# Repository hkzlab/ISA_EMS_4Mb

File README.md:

# ISA 4Mb EMS / ROM Adapter

## Introduction

This is a reimplementation of the **lo-tech.co.uk** [2Mb ISA EMS board](https://www.lo-tech.co.uk/wiki/Lo-tech_2MB_EMS_Board) with small changes:

- All components are thru-hole instead of SMD
- Maximum installable memory expanded to 4Mb
- Activity led to indicate when the memory is accessed
- Optional ROM expansion (had some free space on the PCB...)

### Disclaimer

I take NO responsibility for what happens if you decide to build and use this card. Your computer might crash, catch fire or be destroyed in other nasty ways.
Also, as this card is mostly based on the work of others, You're encourauged to take what you deem fit from this, and use it in your projects!

Additionally, do **NOT CONTACT lo-tech.co.uk FOR SUPPORT**, while this board is derived from their work, it is not their product, please do not waste their time.

## Configuration

### EMS

To configure the EMS, jumpers on J2 header are used.

Pins 1 and 2 configure the Page Frame base address, while 3 and 4 configure the IO Port base address.

```text

EMS Page Frame Base
 1 | 2 | Base  |
---+---+-------+
 X | X | C000h |
---+---+-------+
   | X | D000h |
---+---+-------+
 X |   | E000h |
---+---+-------+
   |   | Inval |
---+---+-------+

EMS IO Port Base
 3 | 4 |   Base     |
---+---+------------+
 X | X |  260-263h  |
---+---+------------+
   | X |  264-267h  |
---+---+------------+
 X |   |  268-26Bh  |
---+---+------------+
   |   |  26C-26Fh  |
---+---+------------+

```

### ROM

To configure the expansion ROM, jumpers on J3 header are used.

The `ENA` pin will enable the ROM when jumpered.

When `32K` pin is jumpered, only 32Kb of the ROM will be used. The ROM can be made to appear at the following addresses:

```text
       | A18 | A17 | A16 | A15 |
-------+-----+-----+-----+-----+
 A000h |  X  |     |  X  |  X  |
-------+-----+-----+-----+-----+
 A800h |  X  |     |  X  |     | (32K only)
-------+-----+-----+-----+-----+
 B000h |  X  |     |     |  X  |
-------+-----+-----+-----+-----+
 B800h |  X  |     |     |     | (32K only)
-------+-----+-----+-----+-----+
 C000h |     |  X  |  X  |  X  |
-------+-----+-----+-----+-----+
 C800h |     |  X  |  X  |     | (32K only)
-------+-----+-----+-----+-----+
 D000h |     |  X  |     |  X  |
-------+-----+-----+-----+-----+
 D800h |     |  X  |     |     | (32K only)
-------+-----+-----+-----+-----+
 E000h |     |     |  X  |  X  |
-------+-----+-----+-----+-----+
 E800h |     |     |  X  |     | (32K only)
-------+-----+-----+-----+-----+
 F000h |     |     |     |  X  |
-------+-----+-----+-----+-----+
 F800h |     |     |     |     | (32K only)
-------+-----+-----+-----+-----+
```

## Usage

You need a **memory manager** to use this board. The original `LTEMM` driver provided by lo-tech only supports up to 2Mb. You can find a modified version under the `software` directory of this repository that supports up to 4Mb (actually 4080Kb or 255 pages, to support all 256 pages I need to rework the detection logic a bit... will get around to it in the future).

## Bill of Materials

All ICs are in DIP package.

If you don't need the expansion ROM feature, you can omit C19, C20, U1, U2, RN1, R1, R2 and J3.

- U1, U7, U8: 74HCT688
- U2: SST39SF010
- U3, U4, U5, U6, U13, U14. U15, U16: AS6C4008 (You don't need to fill all sockets: fit as much memory as you need starting from socket 1!)
- U11: 74HC04 (HCT is fine too)
- U9: 74HCT139
- U10: 74HCT32
- U12: 74ACT245
- U17: 74HCT138
- U18, U19, U20, U21: 74HCT573
- RN1: res. network, 10k, bussed, 6 pins
- RN2: res. network, 10k, bussed, 5 pins
- RN3: res. network, 10k, bussed, 9 pins.
- R1, R2: 10k resistor
- R3: ~470-1k resistor (depends on the type of LED mounted on D1 and desired brightness)
- D1: 3.0mm or 5.0mm LED
- J2 2x4 2.5mm breakable header
- J3 2x7 2.5mm breakable header
- C5, C6: 10uF / 50v electrolytic caps
- Remaining caps: 22x 100nF, ceramic
- ISA bracket: Keystone 9202, plus screws

## Known Issues

I have received reports of this board being unstable when used with some homebrew PC clones, reports included the Xi8088 and NuXT. I have noted similar issues on a Micro8088. On the other hand, an all-CMOS board was tested fine on multiple AT clones I have.
Replacing the following ICs with ones from the TTL family solved the issue for me and for others: U7, U8, U9, U10, U11, U12.

Note that, for increased stability, I use an ISA terminator with these homebrew computers.

Note that the EEPROM U2 has no buffers on the data output. This can cause instability on loaded/noisy buses. Support for the EEPROM will be removed in newer iterations of this board to produce a smaller variant.

## Credits

- Thanks to [lo-tech.co.uk](https://www.lo-tech.co.uk/) for having published their schematics
- Thanks to [Sergey](http://www.malinov.com/Home/sergeys-projects) for all his projects!

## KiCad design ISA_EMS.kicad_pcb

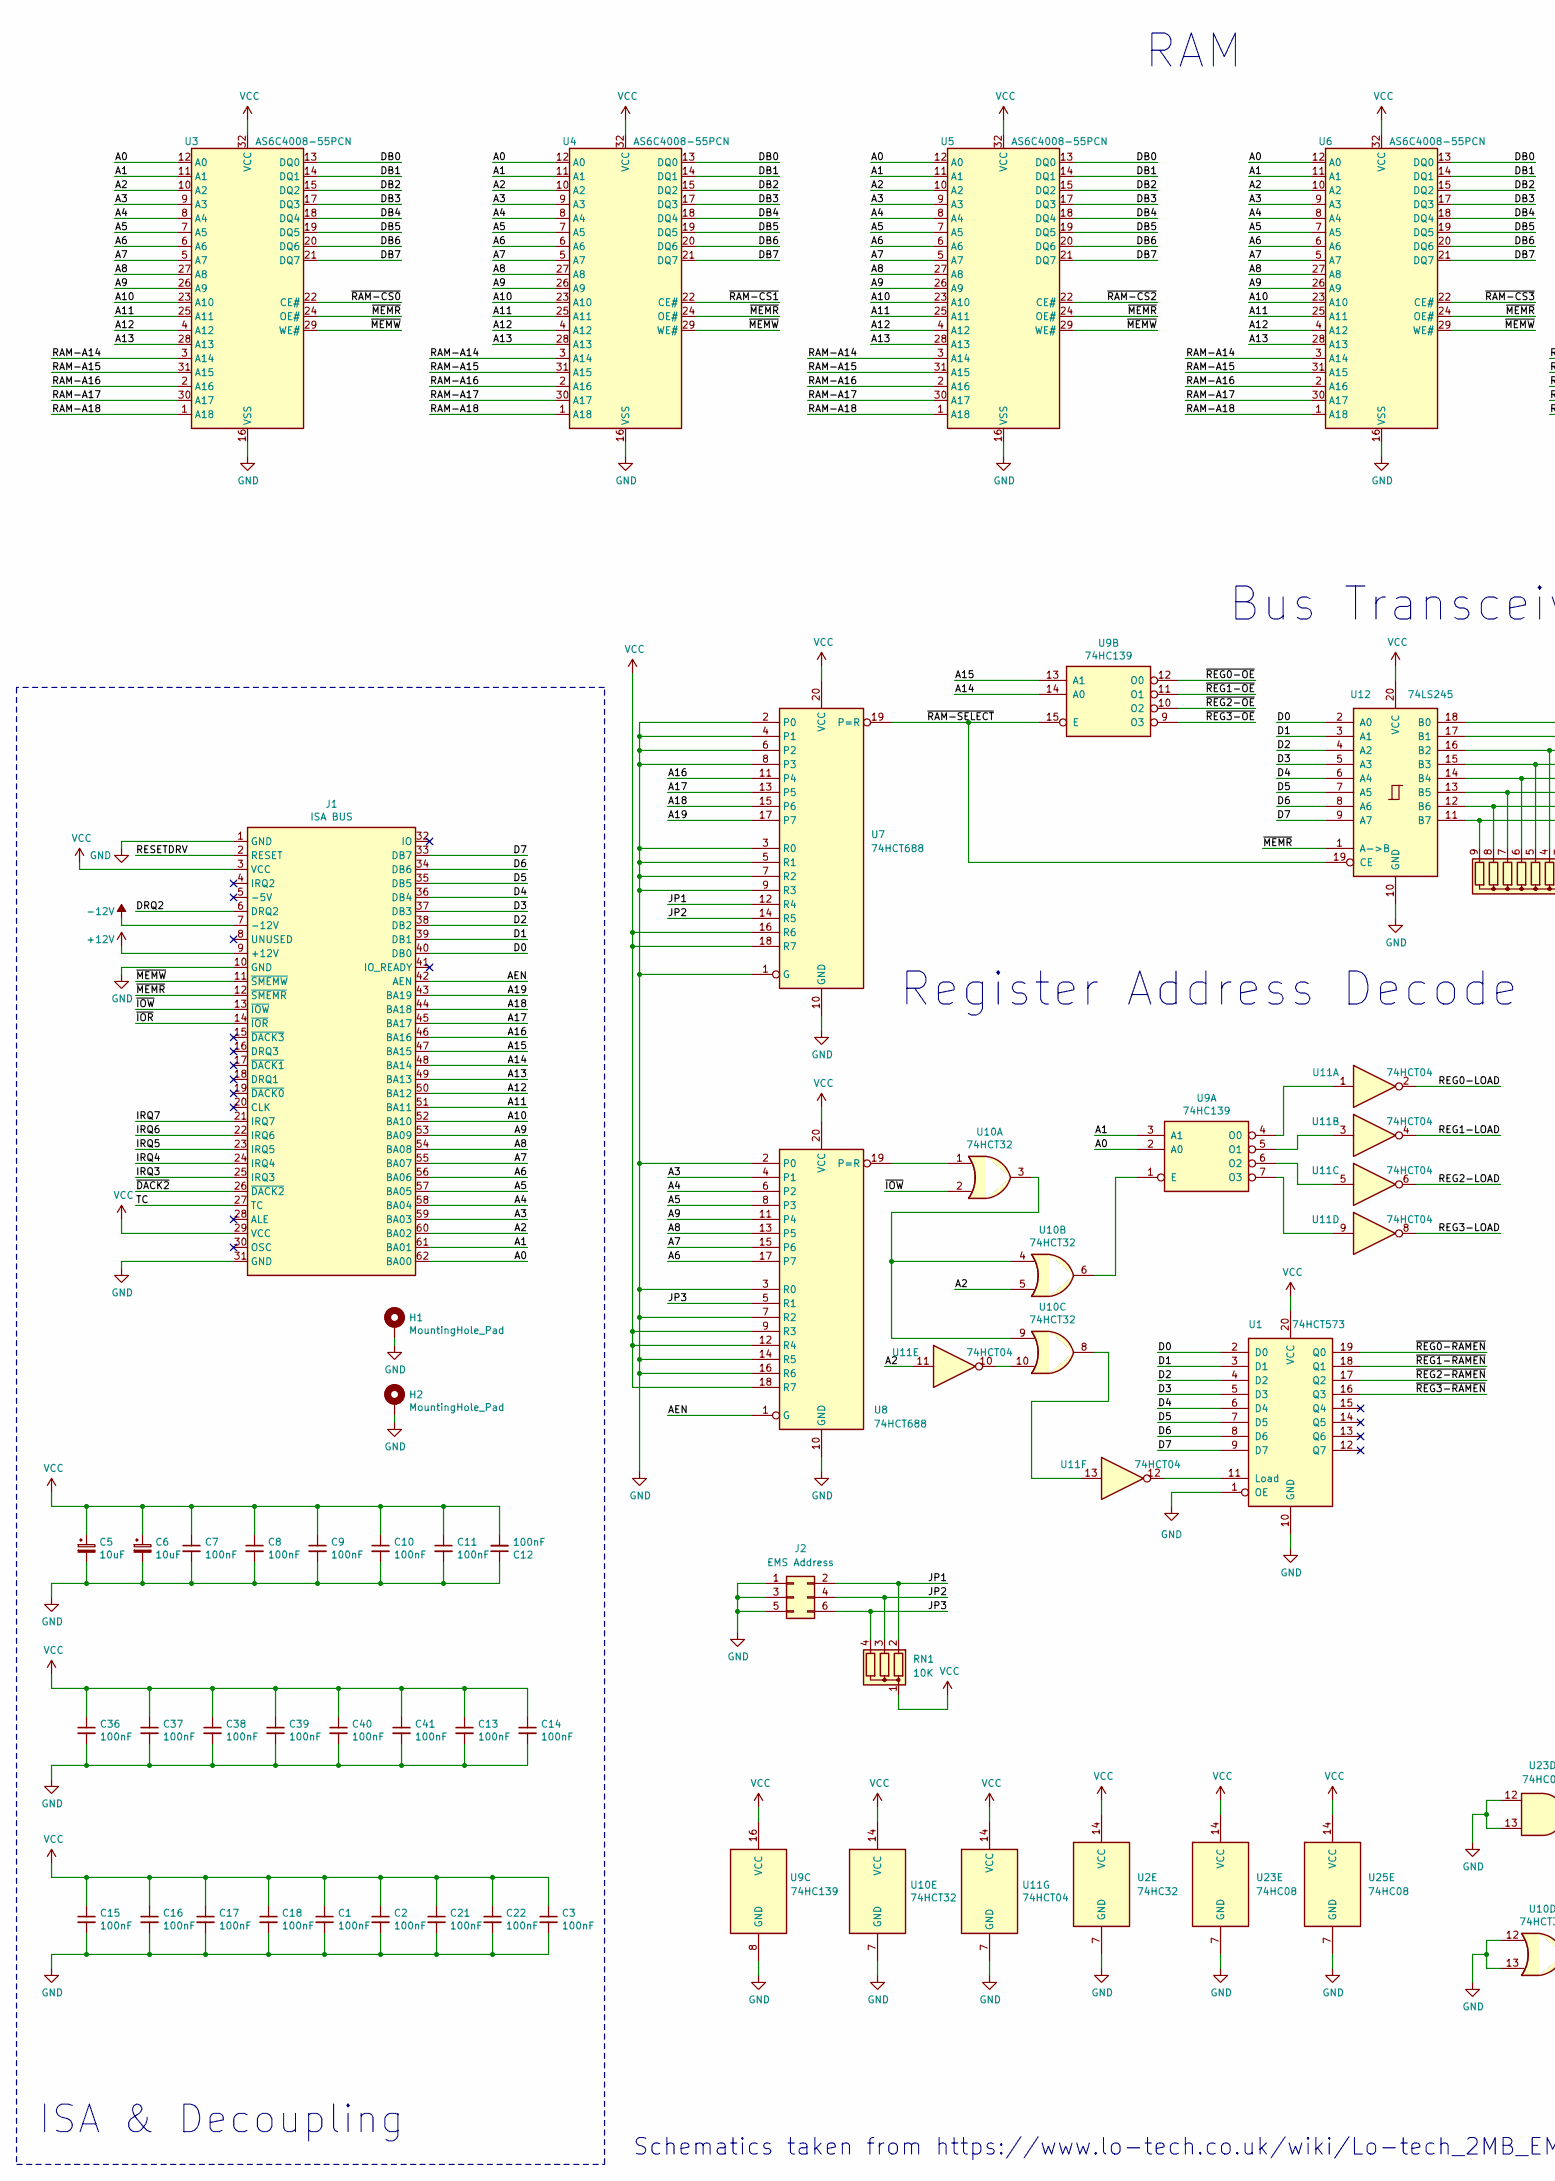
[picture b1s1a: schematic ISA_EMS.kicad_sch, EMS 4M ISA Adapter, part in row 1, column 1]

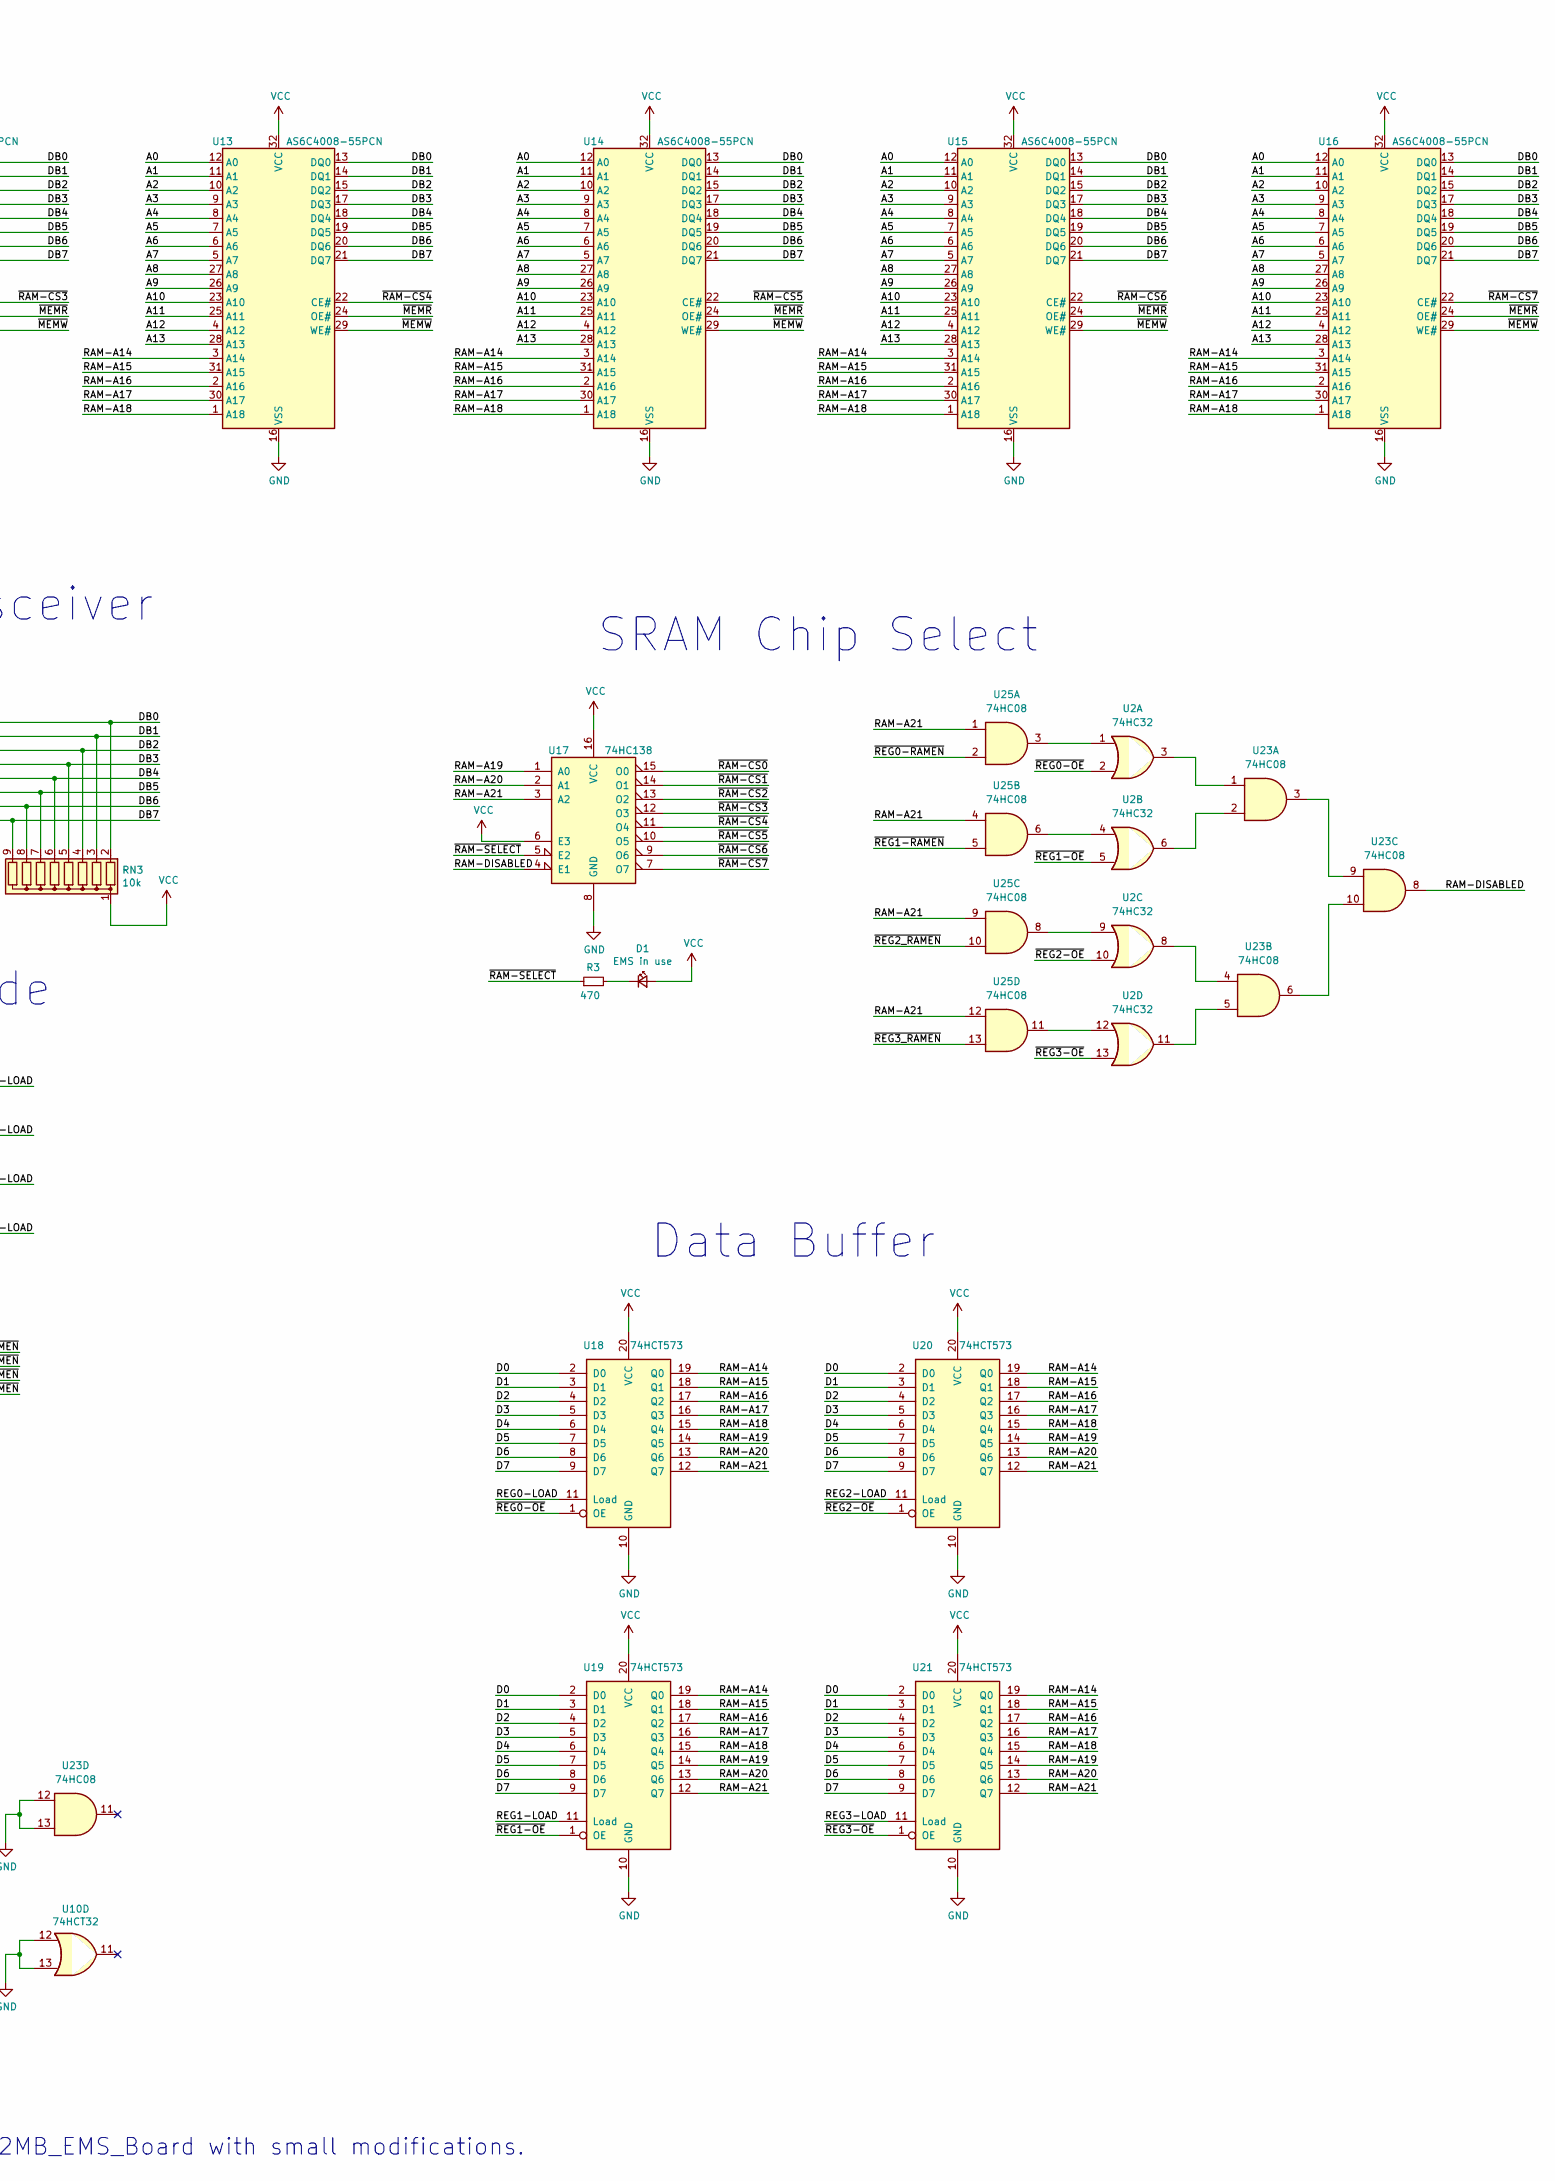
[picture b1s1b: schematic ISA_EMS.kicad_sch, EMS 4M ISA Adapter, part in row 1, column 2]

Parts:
C1, C2, C3, C7, C8, C9, C10, C11, C12, C13, C14, C15, C16, C17, C18, C21, C22, C36, C37, C38, C39, C40, C41: 100nF; C_1206_3216Metric_Pad1.33x1.80mm_HandSolder
C5, C6: 10uF; CP_Radial_D5.0mm_P2.50mm
D1: EMS in use; LED_D3.0mm_Clear
H1, H2: MountingHole_Pad; Hole_3mm
J1: ISA BUS; Conn_Edge_PCB_ISA8
J2: EMS Address; PinHeader_2x03_P2.54mm_Vertical
R3: 470; R_Axial_DIN0207_L6.3mm_D2.5mm_P10.16mm_Horizontal
RN1: 10K; R_Array_SIP4
RN3: 10k; R_Array_SIP9
U1, U18, U19, U20, U21: 74HCT573; DIP-20_W7.62mm
U2: 74HC32; DIP-14_W7.62mm
U3, U4, U5, U6, U13, U14, U15, U16: AS6C4008-55PCN; DIP-32_W15.24mm
U7, U8: 74HCT688; DIP-20_W7.62mm
U9: 74HC139; DIP-16_W7.62mm
U10: 74HCT32; DIP-14_W7.62mm
U11: 74HCT04; DIP-14_W7.62mm
U12: 74LS245; DIP-20_W7.62mm
U17: 74HC138; DIP-16_W7.62mm
U23, U25: 74HC08; DIP-14_W7.62mm

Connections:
+12V: J1.9 (+12V)
-12V: J1.7 (-12V)
/A0: J1.62 (BA00), U3.12 (A0), U4.12 (A0), U5.12 (A0), U6.12 (A0), U9.2 (A0), U13.12 (A0), U14.12 (A0), U15.12 (A0), U16.12 (A0)
/A1: J1.61 (BA01), U3.11 (A1), U4.11 (A1), U5.11 (A1), U6.11 (A1), U9.3 (A1), U13.11 (A1), U14.11 (A1), U15.11 (A1), U16.11 (A1)
/A2: J1.60 (BA02), U3.10 (A2), U4.10 (A2), U5.10 (A2), U6.10 (A2), U10.5, U11.11, U13.10 (A2), U14.10 (A2), U15.10 (A2), U16.10 (A2)
/A3: J1.59 (BA03), U3.9 (A3), U4.9 (A3), U5.9 (A3), U6.9 (A3), U8.4 (P1), U13.9 (A3), U14.9 (A3), U15.9 (A3), U16.9 (A3)
/A4: J1.58 (BA04), U3.8 (A4), U4.8 (A4), U5.8 (A4), U6.8 (A4), U8.6 (P2), U13.8 (A4), U14.8 (A4), U15.8 (A4), U16.8 (A4)
/A5: J1.57 (BA05), U3.7 (A5), U4.7 (A5), U5.7 (A5), U6.7 (A5), U8.8 (P3), U13.7 (A5), U14.7 (A5), U15.7 (A5), U16.7 (A5)
/A6: J1.56 (BA06), U3.6 (A6), U4.6 (A6), U5.6 (A6), U6.6 (A6), U8.17 (P7), U13.6 (A6), U14.6 (A6), U15.6 (A6), U16.6 (A6)
/A7: J1.55 (BA07), U3.5 (A7), U4.5 (A7), U5.5 (A7), U6.5 (A7), U8.15 (P6), U13.5 (A7), U14.5 (A7), U15.5 (A7), U16.5 (A7)
/A8: J1.54 (BA08), U3.27 (A8), U4.27 (A8), U5.27 (A8), U6.27 (A8), U8.13 (P5), U13.27 (A8), U14.27 (A8), U15.27 (A8), U16.27 (A8)
/A9: J1.53 (BA09), U3.26 (A9), U4.26 (A9), U5.26 (A9), U6.26 (A9), U8.11 (P4), U13.26 (A9), U14.26 (A9), U15.26 (A9), U16.26 (A9)
/A10: J1.52 (BA10), U3.23 (A10), U4.23 (A10), U5.23 (A10), U6.23 (A10), U13.23 (A10), U14.23 (A10), U15.23 (A10), U16.23 (A10)
/A11: J1.51 (BA11), U3.25 (A11), U4.25 (A11), U5.25 (A11), U6.25 (A11), U13.25 (A11), U14.25 (A11), U15.25 (A11), U16.25 (A11)
/A12: J1.50 (BA12), U3.4 (A12), U4.4 (A12), U5.4 (A12), U6.4 (A12), U13.4 (A12), U14.4 (A12), U15.4 (A12), U16.4 (A12)
/A13: J1.49 (BA13), U3.28 (A13), U4.28 (A13), U5.28 (A13), U6.28 (A13), U13.28 (A13), U14.28 (A13), U15.28 (A13), U16.28 (A13)
/A14: J1.48 (BA14), U9.14 (A0)
/A15: J1.47 (BA15), U9.13 (A1)
/A16: J1.46 (BA16), U7.11 (P4)
/A17: J1.45 (BA17), U7.13 (P5)
/A18: J1.44 (BA18), U7.15 (P6)
/A19: J1.43 (BA19), U7.17 (P7)
/AEN: J1.42 (AEN), U8.1 (G)
/D0: J1.40 (DB0), U1.2 (D0), U12.2 (A0), U18.2 (D0), U19.2 (D0), U20.2 (D0), U21.2 (D0)
/D1: J1.39 (DB1), U1.3 (D1), U12.3 (A1), U18.3 (D1), U19.3 (D1), U20.3 (D1), U21.3 (D1)
/D2: J1.38 (DB2), U1.4 (D2), U12.4 (A2), U18.4 (D2), U19.4 (D2), U20.4 (D2), U21.4 (D2)
/D3: J1.37 (DB3), U1.5 (D3), U12.5 (A3), U18.5 (D3), U19.5 (D3), U20.5 (D3), U21.5 (D3)
/D4: J1.36 (DB4), U1.6 (D4), U12.6 (A4), U18.6 (D4), U19.6 (D4), U20.6 (D4), U21.6 (D4)
/D5: J1.35 (DB5), U1.7 (D5), U12.7 (A5), U18.7 (D5), U19.7 (D5), U20.7 (D5), U21.7 (D5)
/D6: J1.34 (DB6), U1.8 (D6), U12.8 (A6), U18.8 (D6), U19.8 (D6), U20.8 (D6), U21.8 (D6)
/D7: J1.33 (DB7), U1.9 (D7), U12.9 (A7), U18.9 (D7), U19.9 (D7), U20.9 (D7), U21.9 (D7)
/DB0: RN3.2 (R1), U3.13 (DQ0), U4.13 (DQ0), U5.13 (DQ0), U6.13 (DQ0), U12.18 (B0), U13.13 (DQ0), U14.13 (DQ0), U15.13 (DQ0), U16.13 (DQ0)
/DB1: RN3.3 (R2), U3.14 (DQ1), U4.14 (DQ1), U5.14 (DQ1), U6.14 (DQ1), U12.17 (B1), U13.14 (DQ1), U14.14 (DQ1), U15.14 (DQ1), U16.14 (DQ1)
/DB2: RN3.4 (R3), U3.15 (DQ2), U4.15 (DQ2), U5.15 (DQ2), U6.15 (DQ2), U12.16 (B2), U13.15 (DQ2), U14.15 (DQ2), U15.15 (DQ2), U16.15 (DQ2)
/DB3: RN3.5 (R4), U3.17 (DQ3), U4.17 (DQ3), U5.17 (DQ3), U6.17 (DQ3), U12.15 (B3), U13.17 (DQ3), U14.17 (DQ3), U15.17 (DQ3), U16.17 (DQ3)
/DB4: RN3.6 (R5), U3.18 (DQ4), U4.18 (DQ4), U5.18 (DQ4), U6.18 (DQ4), U12.14 (B4), U13.18 (DQ4), U14.18 (DQ4), U15.18 (DQ4), U16.18 (DQ4)
/DB5: RN3.7 (R6), U3.19 (DQ5), U4.19 (DQ5), U5.19 (DQ5), U6.19 (DQ5), U12.13 (B5), U13.19 (DQ5), U14.19 (DQ5), U15.19 (DQ5), U16.19 (DQ5)
/DB6: RN3.8 (R7), U3.20 (DQ6), U4.20 (DQ6), U5.20 (DQ6), U6.20 (DQ6), U12.12 (B6), U13.20 (DQ6), U14.20 (DQ6), U15.20 (DQ6), U16.20 (DQ6)
/DB7: RN3.9 (R8), U3.21 (DQ7), U4.21 (DQ7), U5.21 (DQ7), U6.21 (DQ7), U12.11 (B7), U13.21 (DQ7), U14.21 (DQ7), U15.21 (DQ7), U16.21 (DQ7)
/DRQ2: J1.6 (DRQ2)
/IRQ3: J1.25 (IRQ3)
/IRQ4: J1.24 (IRQ4)
/IRQ5: J1.23 (IRQ5)
/IRQ6: J1.22 (IRQ6)
/IRQ7: J1.21 (IRQ7)
/JP1: J2.2, RN1.2 (R1), U7.12 (R4)
/JP2: J2.4, RN1.3 (R2), U7.14 (R5)
/JP3: J2.6, RN1.4 (R3), U8.5 (R1)
/RAM-A14: U3.3 (A14), U4.3 (A14), U5.3 (A14), U6.3 (A14), U13.3 (A14), U14.3 (A14), U15.3 (A14), U16.3 (A14), U18.19 (Q0), U19.19 (Q0), U20.19 (Q0), U21.19 (Q0)
/RAM-A15: U3.31 (A15), U4.31 (A15), U5.31 (A15), U6.31 (A15), U13.31 (A15), U14.31 (A15), U15.31 (A15), U16.31 (A15), U18.18 (Q1), U19.18 (Q1), U20.18 (Q1), U21.18 (Q1)
/RAM-A16: U3.2 (A16), U4.2 (A16), U5.2 (A16), U6.2 (A16), U13.2 (A16), U14.2 (A16), U15.2 (A16), U16.2 (A16), U18.17 (Q2), U19.17 (Q2), U20.17 (Q2), U21.17 (Q2)
/RAM-A17: U3.30 (A17), U4.30 (A17), U5.30 (A17), U6.30 (A17), U13.30 (A17), U14.30 (A17), U15.30 (A17), U16.30 (A17), U18.16 (Q3), U19.16 (Q3), U20.16 (Q3), U21.16 (Q3)
/RAM-A18: U3.1 (A18), U4.1 (A18), U5.1 (A18), U6.1 (A18), U13.1 (A18), U14.1 (A18), U15.1 (A18), U16.1 (A18), U18.15 (Q4), U19.15 (Q4), U20.15 (Q4), U21.15 (Q4)
/RAM-A19: U17.1 (A0), U18.14 (Q5), U19.14 (Q5), U20.14 (Q5), U21.14 (Q5)
/RAM-A20: U17.2 (A1), U18.13 (Q6), U19.13 (Q6), U20.13 (Q6), U21.13 (Q6)
/RAM-A21: U17.3 (A2), U18.12 (Q7), U19.12 (Q7), U20.12 (Q7), U21.12 (Q7), U25.1, U25.4, U25.9, U25.12
/RAM-DISABLED: U17.4 (E1), U23.8
/REG0-LOAD: U11.2, U18.11 (Load)
/REG1-LOAD: U11.4, U19.11 (Load)
/REG2-LOAD: U11.6, U20.11 (Load)
/REG3-LOAD: U11.8, U21.11 (Load)
/RESETDRV: J1.2 (RESET)
/TC: J1.27 (TC)
/~DACK2: J1.26 (~DACK2)
/~IOR: J1.14 (~IOR)
/~IOW: J1.13 (~IOW), U10.2
/~MEMR: J1.12 (~SMEMR), U3.24 (OE#), U4.24 (OE#), U5.24 (OE#), U6.24 (OE#), U12.1 (A->B), U13.24 (OE#), U14.24 (OE#), U15.24 (OE#), U16.24 (OE#)
/~MEMW: J1.11 (~SMEMW), U3.29 (WE#), U4.29 (WE#), U5.29 (WE#), U6.29 (WE#), U13.29 (WE#), U14.29 (WE#), U15.29 (WE#), U16.29 (WE#)
/~RAM-CS0: U3.22 (CE#), U17.15 (O0)
/~RAM-CS1: U4.22 (CE#), U17.14 (O1)
/~RAM-CS2: U5.22 (CE#), U17.13 (O2)
/~RAM-CS3: U6.22 (CE#), U17.12 (O3)
/~RAM-CS4: U13.22 (CE#), U17.11 (O4)
/~RAM-CS5: U14.22 (CE#), U17.10 (O5)
/~RAM-CS6: U15.22 (CE#), U17.9 (O6)
/~RAM-CS7: U16.22 (CE#), U17.7 (O7)
/~RAM-SELECT: R3.1, U7.19 (P=R), U9.15 (E), U12.19 (CE), U17.5 (E2)
/~REG0-OE: U2.2, U9.12 (O0), U18.1 (OE)
/~REG0-RAMEN: U1.19 (Q0), U25.2
/~REG1-OE: U2.5, U9.11 (O1), U19.1 (OE)
/~REG1-RAMEN: U1.18 (Q1), U25.5
/~REG2-OE: U2.10, U9.10 (O2), U20.1 (OE)
/~REG2-RAMEN: U1.17 (Q2)
/~REG2_RAMEN: U25.10
/~REG3-OE: U2.13, U9.9 (O3), U21.1 (OE)
/~REG3-RAMEN: U1.16 (Q3)
/~REG3_RAMEN: U25.13
GND: C1.2, C2.2, C3.2, C5.2, C6.2, C7.2, C8.2, C9.2, C10.2, C11.2, C12.1, C13.2, C14.2, C15.2, C16.2, C17.2, C18.2, C21.2, C22.2, C36.2, C37.2, C38.2, C39.2, C40.2, C41.2, H1.1, H2.1, J1.1 (GND), J1.10 (GND), J1.31 (GND), J2.1, J2.3, J2.5, U1.1 (OE), U1.10 (GND), U2.7 (GND), U3.16 (VSS), U4.16 (VSS), U5.16 (VSS), U6.16 (VSS), U7.1 (G), U7.2 (P0), U7.3 (R0), U7.4 (P1), U7.5 (R1), U7.6 (P2), U7.7 (R2), U7.8 (P3), U7.9 (R3), U7.10 (GND), U8.2 (P0), U8.3 (R0), U8.7 (R2), U8.10 (GND), U8.14 (R5), U8.16 (R6), U9.8 (GND), U10.7 (GND), U10.12, U10.13, U11.7 (GND), U12.10 (GND), U13.16 (VSS), U14.16 (VSS), U15.16 (VSS), U16.16 (VSS), U17.8 (GND), U18.10 (GND), U19.10 (GND), U20.10 (GND), U21.10 (GND), U23.7 (GND), U23.12, U23.13, U25.7 (GND)
unnamed: D1.1 (K), R3.2
unnamed: U1.11 (Load), U11.12
unnamed: U2.1, U25.3
unnamed: U2.3, U23.1
unnamed: U2.4, U25.6
unnamed: U2.6, U23.2
unnamed: U2.8, U23.4
unnamed: U2.9, U25.8
unnamed: U2.11, U23.5
unnamed: U2.12, U25.11
unnamed: U8.19 (P=R), U10.1
unnamed: U9.1 (E), U10.6
unnamed: U9.4 (O0), U11.1
unnamed: U9.5 (O1), U11.3
unnamed: U9.6 (O2), U11.5
unnamed: U9.7 (O3), U11.9
unnamed: U10.3, U10.4, U10.9
unnamed: U10.8, U11.13
unnamed: U10.10, U11.10
unnamed: U23.3, U23.9
unnamed: U23.6, U23.10
VCC: C1.1, C2.1, C3.1, C5.1, C6.1, C7.1, C8.1, C9.1, C10.1, C11.1, C12.2, C13.1, C14.1, C15.1, C16.1, C17.1, C18.1, C21.1, C22.1, C36.1, C37.1, C38.1, C39.1, C40.1, C41.1, D1.2 (A), J1.3 (VCC), J1.29 (VCC), RN1.1 (common), RN3.1 (common), U1.20 (VCC), U2.14 (VCC), U3.32 (VCC), U4.32 (VCC), U5.32 (VCC), U6.32 (VCC), U7.16 (R6), U7.18 (R7), U7.20 (VCC), U8.9 (R3), U8.12 (R4), U8.18 (R7), U8.20 (VCC), U9.16 (VCC), U10.14 (VCC), U11.14 (VCC), U12.20 (VCC), U13.32 (VCC), U14.32 (VCC), U15.32 (VCC), U16.32 (VCC), U17.6 (E3), U17.16 (VCC), U18.20 (VCC), U19.20 (VCC), U20.20 (VCC), U21.20 (VCC), U23.14 (VCC), U25.14 (VCC)

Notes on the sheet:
SRAM Chip Select
ISA & Decoupling
Data Buffer
Register Address Decode
RAM
Bus Transceiver
Schematics taken from https://www.lo-tech.co.uk/wiki/Lo-tech_2MB_EMS_Board with small modifications.

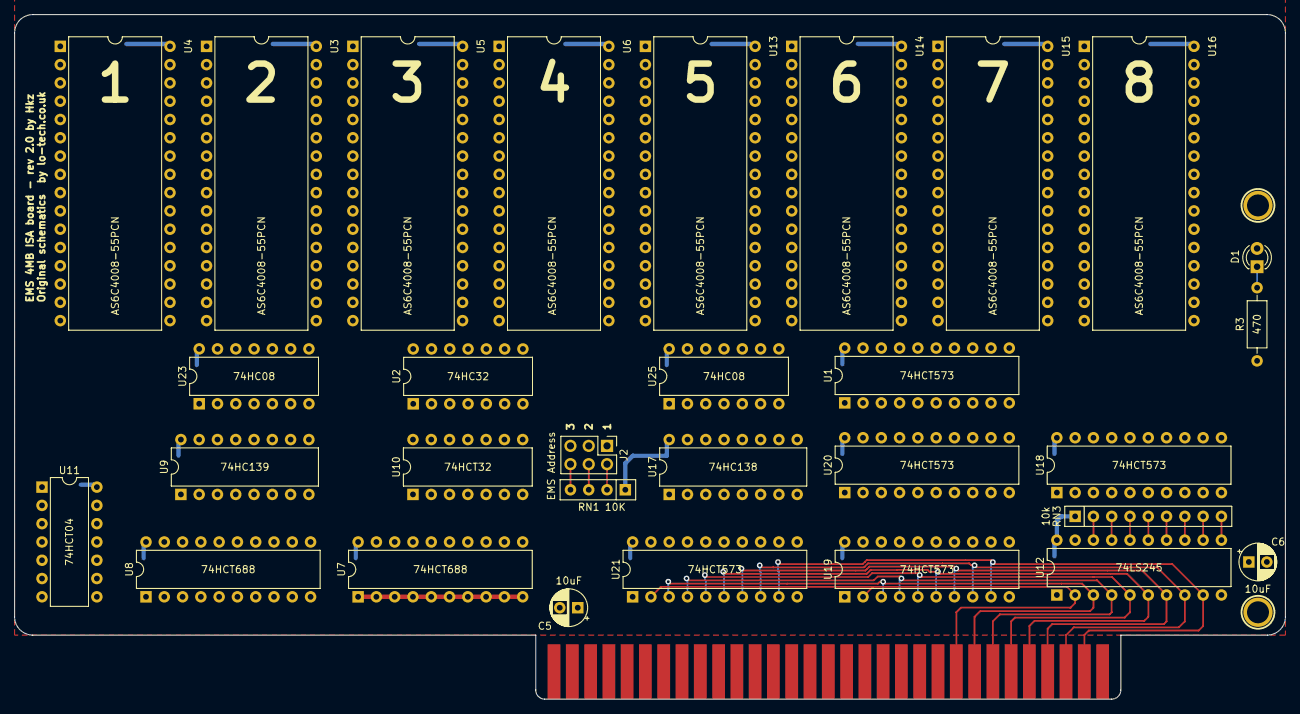
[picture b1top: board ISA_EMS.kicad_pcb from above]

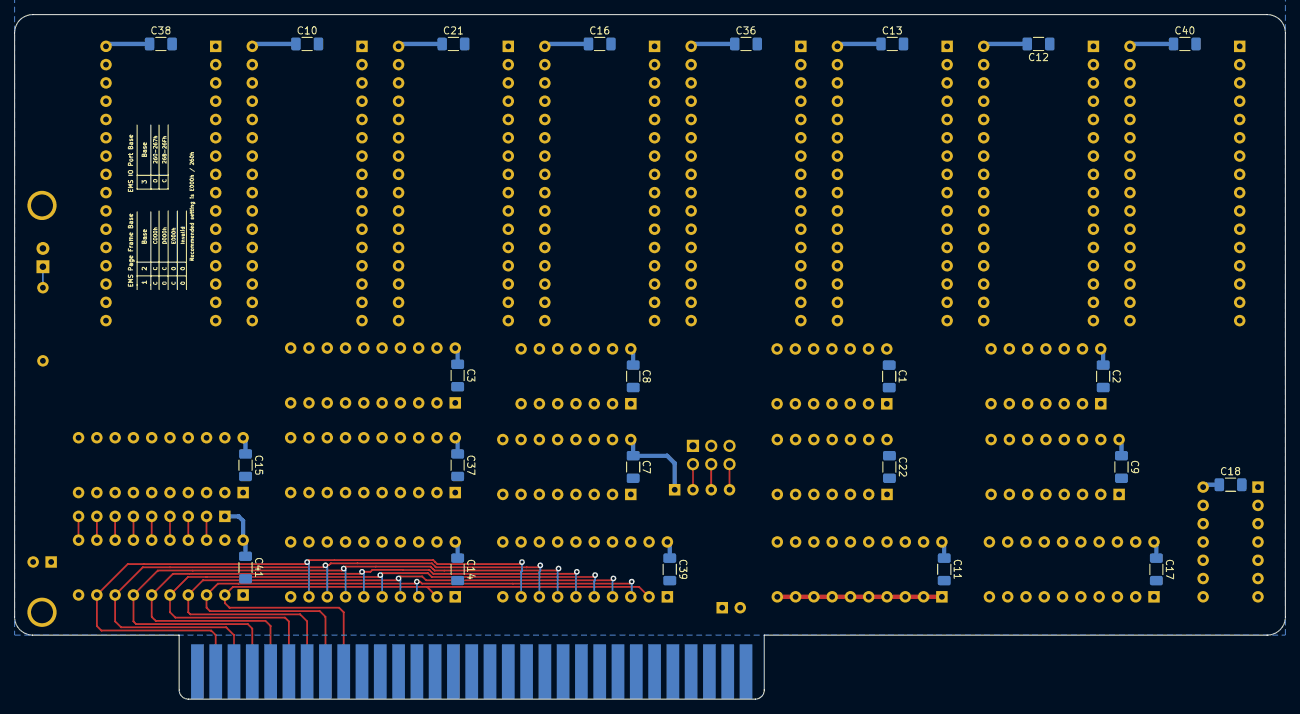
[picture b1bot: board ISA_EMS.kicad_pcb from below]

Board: 2 copper layers, 176.5 x 95.1 mm, 56 parts (23 on the bottom side), 94 nets.

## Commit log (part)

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2021-02-24 Import files
2021-02-24 Add first ram CHIP
2021-02-24 Add all the necessary RAM chips
2021-02-24 Import schematics from lo-tech ems board
2021-02-24 Update schematic, draw board
2021-02-24 Routed the board
2021-02-24 Update the silkscreen
2021-02-24 Added missing cap
2021-02-25 Reorganize board a bit
2021-02-25 Redoing silkscreen
2021-02-25 Updated silkscreen
2021-02-25 Update gerber
2021-02-25 Add notes to schematics
2021-03-19 Add README and software
2021-03-19 Rename directory
2021-03-19 Add components to be omitted to remove ROM function
2021-03-19 Add a list in credits
2021-03-19 Add BOM
2021-04-06 Updated readme notes
2021-04-06 Updated readme again
2021-05-06 Removed BOOTROM, make board smaller, reroute
2021-05-06 Reroute some traces
2021-11-09 Update KiCad URL
2022-11-05 Correct BoM for U17
2023-10-14 Initial import to KiCad 7
2024-11-19 Add register to disable RAM ICs circuitry
2024-11-19 Disable upper memory per-window
2024-11-19 Upda type of some ICs
2024-11-19 Updated schematic
2024-11-19 Replace components on board
2024-11-19 Begin routing
